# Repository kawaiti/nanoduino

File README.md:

nanoduino
=========

nanoduino project

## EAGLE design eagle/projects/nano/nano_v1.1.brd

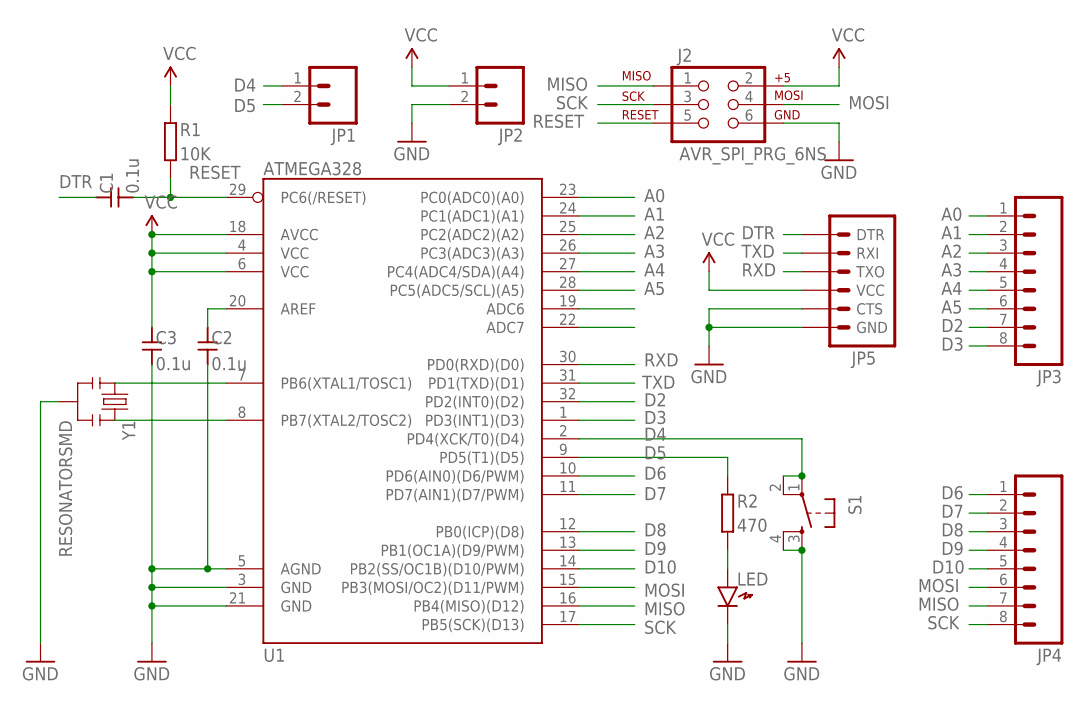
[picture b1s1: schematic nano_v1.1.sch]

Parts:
C1, C2, C3: 0.1u; SMD1608
J2: AVR_SPI_PRG_6NS; 2X3-NS
JP1, JP2: M02PTH; 1X02
JP3, JP4: M081X08; 1X08
JP5: ARDUINO_SERIAL_PROGRAMPTH; 1X06
LED: LED1608
R1: 10K; SMD1608
R2: 470; SMD1608
S1: TAC_SWITCHSMD; TACTILE_SWITCH_SMD
U1: ATMEGA328; TQFP32-08
Y1: RESONATORSMD; RESONATOR-SMD

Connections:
A0: JP3.1, U1.23 (PC0(ADC0)(A0))
A1: JP3.2, U1.24 (PC1(ADC1)(A1))
A2: JP3.3, U1.25 (PC2(ADC2)(A2))
A3: JP3.4, U1.26 (PC3(ADC3)(A3))
A4: JP3.5, U1.27 (PC4(ADC4/SDA)(A4))
A5: JP3.6, U1.28 (PC5(ADC5/SCL)(A5))
D2: JP3.7, U1.32 (PD2(INT0)(D2))
D3: JP3.8, U1.1 (PD3(INT1)(D3))
D4: JP1.1, S1.1, S1.2, U1.2 (PD4(XCK/T0)(D4))
D5: JP1.2, R2.1, U1.9 (PD5(T1)(D5))
D6: JP4.1, U1.10 (PD6(AIN0)(D6/PWM))
D7: JP4.2, U1.11 (PD7(AIN1)(D7/PWM))
D8: JP4.3, U1.12 (PB0(ICP)(D8))
D9: JP4.4, U1.13 (PB1(OC1A)(D9/PWM))
D10: JP4.5, U1.14 (PB2(SS/OC1B)(D10/PWM))
DTR: C1.1, JP5.1 (DTR)
GND: C2.2, C3.2, J2.6, JP2.2, JP5.5 (CTS), JP5.6 (GND), LED.K, S1.3, S1.4, U1.3 (GND), U1.5 (AGND), U1.21 (GND), Y1.2
MISO: J2.1, JP4.7, U1.16 (PB4(MISO)(D12))
MOSI: J2.4, JP4.6, U1.15 (PB3(MOSI/OC2)(D11/PWM))
unnamed: LED.A, R2.2
unnamed: C2.1, U1.20 (AREF)
unnamed: U1.8 (PB7(XTAL2/TOSC2)), Y1.3
unnamed: U1.7 (PB6(XTAL1/TOSC1)), Y1.1
RESET: C1.2, J2.5, R1.2, U1.29 (PC6(/RESET))
RXD: JP5.3 (TXO), U1.30 (PD0(RXD)(D0))
SCK: J2.3, JP4.8, U1.17 (PB5(SCK)(D13))
TXD: JP5.2 (RXI), U1.31 (PD1(TXD)(D1))
VCC: C3.1, J2.2, JP2.1, JP5.4 (VCC), R1.1, U1.4 (VCC), U1.6 (VCC), U1.18 (AVCC)

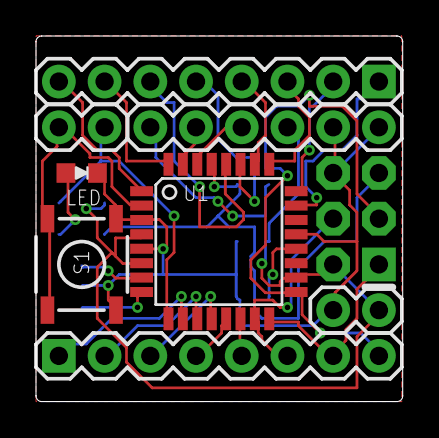
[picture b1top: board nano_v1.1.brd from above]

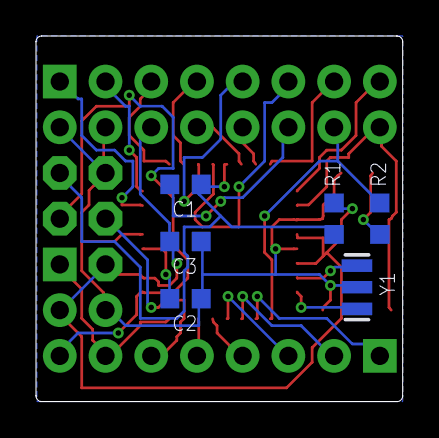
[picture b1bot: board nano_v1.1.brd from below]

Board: 2 copper layers, 20.4 x 20.3 mm, 15 parts (6 on the bottom side), 28 nets.

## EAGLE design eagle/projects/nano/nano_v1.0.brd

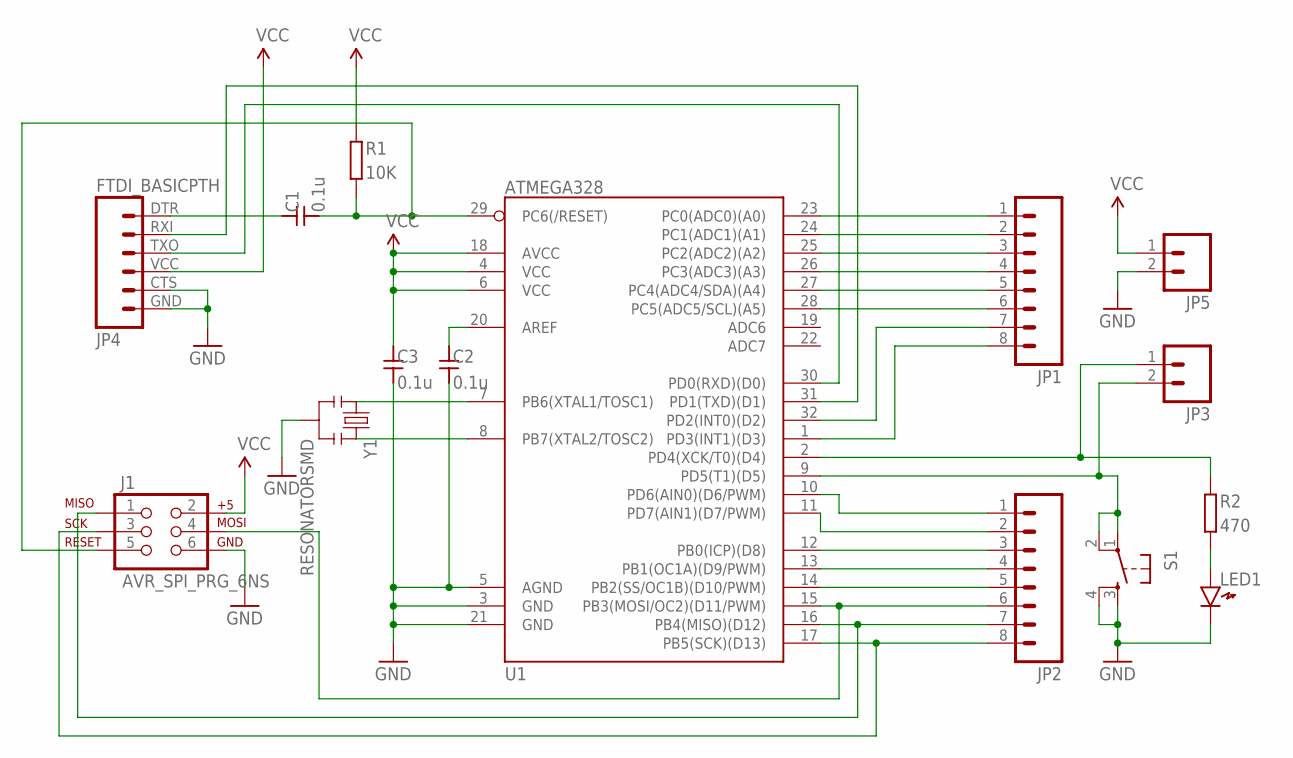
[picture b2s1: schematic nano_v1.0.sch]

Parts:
C1, C2, C3: 0.1u; SMD2012
J1: AVR_SPI_PRG_6NS; 2X3-NS
JP1, JP2: M081X08; 1X08
JP3: M02PTH; 1X02
JP4: FTDI_BASICPTH; FTDI_BASIC
JP5: M021X02_NO_SILK; 1X02_NO_SILK
LED1: LED2012
R1: 10K; SMD2012
R2: 470; SMD2012
S1: TAC_SWITCHSMD; TACTILE_SWITCH_SMD
U1: ATMEGA328; TQFP32-08
Y1: RESONATORSMD; RESONATOR-SMD

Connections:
GND: C2.2, C3.2, J1.6, JP4.CTS (5), JP4.GND (6), JP5.2, LED1.K, S1.3, S1.4, U1.3 (GND), U1.5 (AGND), U1.21 (GND), Y1.2
unnamed: J1.3, JP2.8, U1.17 (PB5(SCK)(D13))
unnamed: J1.1, JP2.7, U1.16 (PB4(MISO)(D12))
unnamed: J1.4, JP2.6, U1.15 (PB3(MOSI/OC2)(D11/PWM))
unnamed: JP2.5, U1.14 (PB2(SS/OC1B)(D10/PWM))
unnamed: JP2.4, U1.13 (PB1(OC1A)(D9/PWM))
unnamed: JP2.3, U1.12 (PB0(ICP)(D8))
unnamed: JP2.2, U1.11 (PD7(AIN1)(D7/PWM))
unnamed: JP2.1, U1.10 (PD6(AIN0)(D6/PWM))
unnamed: JP1.1, U1.23 (PC0(ADC0)(A0))
unnamed: JP1.2, U1.24 (PC1(ADC1)(A1))
unnamed: JP1.3, U1.25 (PC2(ADC2)(A2))
unnamed: JP1.4, U1.26 (PC3(ADC3)(A3))
unnamed: JP1.5, U1.27 (PC4(ADC4/SDA)(A4))
unnamed: JP1.6, U1.28 (PC5(ADC5/SCL)(A5))
unnamed: JP4.TXO (3), U1.30 (PD0(RXD)(D0))
unnamed: JP4.RXI (2), U1.31 (PD1(TXD)(D1))
unnamed: C1.2, J1.5, R1.2, U1.29 (PC6(/RESET))
unnamed: JP3.2, S1.1, S1.2, U1.9 (PD5(T1)(D5))
unnamed: JP1.7, U1.32 (PD2(INT0)(D2))
unnamed: JP1.8, U1.1 (PD3(INT1)(D3))
unnamed: C2.1, U1.20 (AREF)
unnamed: U1.7 (PB6(XTAL1/TOSC1)), Y1.1
unnamed: U1.8 (PB7(XTAL2/TOSC2)), Y1.3
unnamed: C1.1, JP4.DTR (1)
unnamed: JP3.1, R2.1, U1.2 (PD4(XCK/T0)(D4))
unnamed: LED1.A, R2.2
VCC: C3.1, J1.2, JP4.VCC (4), JP5.1, R1.1, U1.4 (VCC), U1.6 (VCC), U1.18 (AVCC)

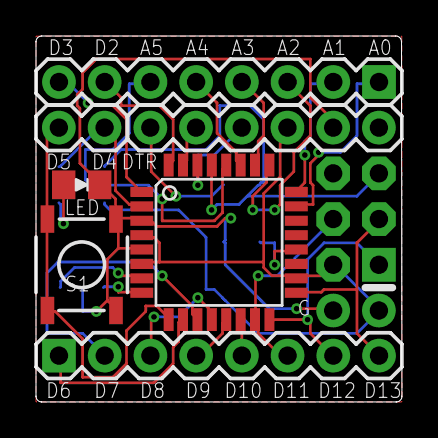
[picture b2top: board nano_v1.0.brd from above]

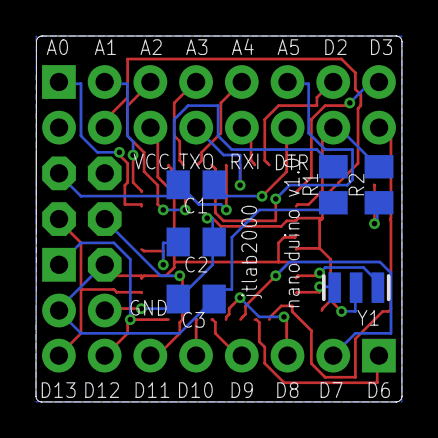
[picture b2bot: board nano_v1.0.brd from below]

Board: 2 copper layers, 20.3 x 20.3 mm, 15 parts (6 on the bottom side), 28 nets.

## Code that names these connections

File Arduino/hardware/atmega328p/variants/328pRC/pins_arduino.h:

/*
  pins_arduino.h - Pin definition functions for Arduino
  Part of Arduino - http://www.arduino.cc/

  Copyright (c) 2007 David A. Mellis

  This library is free software; you can redistribute it and/or
  modify it under the terms of the GNU Lesser General Public
  License as published by the Free Software Foundation; either
  version 2.1 of the License, or (at your option) any later version.

  This library is distributed in the hope that it will be useful,
  but WITHOUT ANY WARRANTY; without even the implied warranty of
  MERCHANTABILITY or FITNESS FOR A PARTICULAR PURPOSE.  See the GNU
  Lesser General Public License for more details.

  You should have received a copy of the GNU Lesser General
  Public License along with this library; if not, write to the
  Free Software Foundation, Inc., 59 Temple Place, Suite 330,
  Boston, MA  02111-1307  USA

  $Id: wiring.h 249 2007-02-03 16:52:51Z mellis $
*/

#ifndef Pins_Arduino_h
#define Pins_Arduino_h

#include <avr/pgmspace.h>

#define NUM_DIGITAL_PINS            22
#define NUM_ANALOG_INPUTS           6
#define analogInputToDigitalPin(p)  ((p < 6) ? (p) + 14 : -1)

#if defined(__AVR_ATmega8__)
#define digitalPinHasPWM(p)         ((p) == 9 || (p) == 10 || (p) == 11)
#else
#define digitalPinHasPWM(p)         ((p) == 3 || (p) == 5 || (p) == 6 || (p) == 9 || (p) == 10 || (p) == 11)
#endif

static const uint8_t SS   = 10;
static const uint8_t MOSI = 11;
static const uint8_t MISO = 12;
static const uint8_t SCK  = 13;

static const uint8_t SDA = 18;
static const uint8_t SCL = 19;
static const uint8_t LED_BUILTIN = 13;

static const uint8_t A0 = 14;
static const uint8_t A1 = 15;
static const uint8_t A2 = 16;
static const uint8_t A3 = 17;
static const uint8_t A4 = 18;
static const uint8_t A5 = 19;
static const uint8_t A6 = 20;
static const uint8_t A7 = 21;

#define digitalPinToPCICR(p)    (((p) >= 0 && (p) <= 21) ? (&PCICR) : ((uint8_t *)0))
#define digitalPinToPCICRbit(p) (((p) <= 7) ? 2 : (((p) <= 13) ? 0 : 1))
#define digitalPinToPCMSK(p)    (((p) <= 7) ? (&PCMSK2) : (((p) <= 13) ? (&PCMSK0) : (((p) <= 21) ? (&PCMSK1) : ((uint8_t *)0))))
#define digitalPinToPCMSKbit(p) (((p) <= 7) ? (p) : (((p) <= 13) ? ((p) - 8) : ((p) - 14)))

#ifdef ARDUINO_MAIN

// On the Arduino board, digital pins are also used
// for the analog output (software PWM).  Analog input
// pins are a separate set.

// ATMEL ATMEGA8 & 168 / ARDUINO
//
//                  +-\/-+
//            PC6  1|    |28  PC5 (AI 5)
//      (D 0) PD0  2|    |27  PC4 (AI 4)
//      (D 1) PD1  3|    |26  PC3 (AI 3)
//      (D 2) PD2  4|    |25  PC2 (AI 2)
// PWM+ (D 3) PD3  5|    |24  PC1 (AI 1)
//      (D 4) PD4  6|    |23  PC0 (AI 0)
//            VCC  7|    |22  GND
//            GND  8|    |21  AREF
//            PB6  9|    |20  AVCC
//            PB7 10|    |19  PB5 (D 13)
// PWM+ (D 5) PD5 11|    |18  PB4 (D 12)
// PWM+ (D 6) PD6 12|    |17  PB3 (D 11) PWM
//      (D 7) PD7 13|    |16  PB2 (D 10) PWM
//      (D 8) PB0 14|    |15  PB1 (D 9) PWM
//                  +----+
//
// (PWM+ indicates the additional PWM pins on the ATmega168.)

// ATMEL ATMEGA1280 / ARDUINO
//
// 0-7 PE0-PE7   works
// 8-13 PB0-PB5  works
// 14-21 PA0-PA7 works 
// 22-29 PH0-PH7 works
// 30-35 PG5-PG0 works
// 36-43 PC7-PC0 works
// 44-51 PJ7-PJ0 works
// 52-59 PL7-PL0 works
// 60-67 PD7-PD0 works
// A0-A7 PF0-PF7
// A8-A15 PK0-PK7


// these arrays map port names (e.g. port B) to the
// appropriate addresses for various functions (e.g. reading
// and writing)
const uint16_t PROGMEM port_to_mode_PGM[] = {
	NOT_A_PORT,
	NOT_A_PORT,
	(uint16_t) &DDRB,
	(uint16_t) &DDRC,
	(uint16_t) &DDRD,
};

const uint16_t PROGMEM port_to_output_PGM[] = {
	NOT_A_PORT,
	NOT_A_PORT,
	(uint16_t) &PORTB,
	(uint16_t) &PORTC,
	(uint16_t) &PORTD,
};

const uint16_t PROGMEM port_to_input_PGM[] = {
	NOT_A_PORT,
	NOT_A_PORT,
	(uint16_t) &PINB,
	(uint16_t) &PINC,
	(uint16_t) &PIND,
};

const uint8_t PROGMEM digital_pin_to_port_PGM[] = {
	PD, /* 0 */
	PD,
	PD,
	PD,
	PD,
	PD,
	PD,
	PD,
	PB, /* 8 */
	PB,
	PB,
	PB,
	PB,
	PB,
	PC, /* 14 */
	PC,
	PC,
	PC,
	PC,
	PC,
  PB, //XTAL1
  PB, //XTAL2
};

const uint8_t PROGMEM digital_pin_to_bit_mask_PGM[] = {
	_BV(0), /* 0, port D */
	_BV(1),
	_BV(2),
	_BV(3),
	_BV(4),
	_BV(5),
	_BV(6),
	_BV(7),
	_BV(0), /* 8, port B */
	_BV(1),
	_BV(2),
	_BV(3),
	_BV(4),
	_BV(5),
	_BV(0), /* 14, port C */
	_BV(1),
	_BV(2),
	_BV(3),
	_BV(4),
	_BV(5),
  _BV(6), //XTAL1
  _BV(7), //XTAL2
};

const uint8_t PROGMEM digital_pin_to_timer_PGM[] = {
	NOT_ON_TIMER, /* 0 - port D */
	NOT_ON_TIMER,
	NOT_ON_TIMER,
	// on the ATmega168, digital pin 3 has hardware pwm
#if defined(__AVR_ATmega8__)
	NOT_ON_TIMER,
#else
	TIMER2B,
#endif
	NOT_ON_TIMER,
	// on the ATmega168, digital pins 5 and 6 have hardware pwm
#if defined(__AVR_ATmega8__)
	NOT_ON_TIMER,
	NOT_ON_TIMER,
#else
	TIMER0B,
	TIMER0A,
#endif
	NOT_ON_TIMER,
	NOT_ON_TIMER, /* 8 - port B */
	TIMER1A,
	TIMER1B,
#if defined(__AVR_ATmega8__)
	TIMER2,
#else
	TIMER2A,
#endif
	NOT_ON_TIMER,
	NOT_ON_TIMER,
	NOT_ON_TIMER,
	NOT_ON_TIMER, /* 14 - port C */
	NOT_ON_TIMER,
	NOT_ON_TIMER,
	NOT_ON_TIMER,
	NOT_ON_TIMER,
};

#endif

#endif

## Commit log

2013-04-21 add nanoduino files

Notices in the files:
parts and their libraries:
SparkFun-Connectors: Licensing: CC v3.0 Share-Alike You are welcome to use this library for commercial purposes.
